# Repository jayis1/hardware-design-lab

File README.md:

# Hardware Design Lab

Author: jayis1

Full-cycle, open-source hardware device designs — from concept to KiCad schematics to production firmware to companion mobile apps. Every device is fully open: schematics, board layouts, C/Python firmware, and React Native apps. Each device lives in its own subfolder with complete deliverables.

## What's Inside Every Device

Every device folder contains the full stack — not just docs, but real buildable artifacts:

| Category | Files | Description |
|---|---|---|
| **Engineering Docs** | `phase1_conceptual_architecture.md` → `phase4_software_stack.md` | 4-phase design process: requirements, BOM & netlists, PCB layout rules, software stack |
| **KiCad Schematics** | `kicad/*.kicad_pro`, `*.kicad_sch`, `*.kicad_pcb` | Full schematic with real component symbols, net labels, power flags, and board outline with placed footprints |
| **C/Python Firmware** | `firmware/main.c`, `registers.h`, `board.h`, `drivers/`, `Makefile` | Production-quality MCU firmware — init code, drivers with DMA, USB descriptors, wire protocol |
| **React Native App** | `app/App.js`, `screens/`, `components/`, `utils/protocol.js`, `package.json` | Companion mobile app for device control, configuration, and status display |

## Design Methodology

Every device follows the same rigorous 4-phase process:

| Phase | Document | Contents |
|---|---|---|
| **Phase 1** | `phase1_conceptual_architecture.md` | Purpose, performance targets, constraints, block diagram, bus topology, power domains |
| **Phase 2** | `phase2_component_selection_schematics.md` | BOM with real part numbers, pinouts/MUX tables, decoupling networks, netlists, impedance matching |
| **Phase 3** | `phase3_pcb_blueprints_layout.md` | PCB stackup, routing rules, length matching, via strategy, thermal management, DFM notes |
| **Phase 4** | `phase4_software_stack.md` | MMIO/register defs, clock & GPIO init (production C), critical device driver, device tree, bootloader |

## Devices

| # | Device | Status | Description |
|---|---|---|---|
| 1 | [`eag-7000/`](eag-7000/) — Edge AI Gateway | ✅ Docs complete, KiCad/firmware/app pending | i.MX8MP + Hailo-8 NPU, 30 TOPS, fanless industrial, 2×2.5GbE, CAN-FD |
| 2 | [`chronos-rtk/`](chronos-rtk/) — Dual-Frequency RTK GNSS Receiver | ✅ Complete | ZED-F9P + STM32L4 + LoRa mesh, cm-level positioning, 868/915 MHz ISM |
| 3 | [`vortex-sdr/`](vortex-sdr/) — Portable SDR Spectrum Analyzer | ✅ Complete | STM32H743 + iCE40UP5K FPGA + ADF4351 PLL, 100kHz–6GHz, dual-FFT waterfall |
| 4 | [`web-slack-ledger/`](web-slack-ledger/) — WebSlack Ledger | Build-tested prototype; physical validation pending | Two-encoder differential travel and reversal ledger for slow hand-fed strip fixtures |
| 5 | [`slip-window/`](slip-window/) — Slip Window | Build-tested prototype; physical validation pending | Slip-casting cradle residence, interrupted draining, longest drain segment, and mold-opening notebook |
| 6 | [`stencil-orbit/`](stencil-orbit/) — Stencil Orbit | Build-tested prototype; physical validation pending | Manual screen-printing carousel station index, registration continuity and per-station tool-use notebook |
| 7 | [`crossover-track/`](crossover-track/) — Crossover Track | Build-tested prototype; physical validation pending | Four-contact cart trial recorder and guided ABBA lane-swap comparison separating cart and lane time contrasts |
| 8 | [`takeup-atlas/`](takeup-atlas/) — Takeup Atlas | Build-tested prototype; physical validation pending | Two-shaft reversal trials recording first output response, three-edge confirmation and rejected attempts in hand-operated mechanisms |
| 9 | [`chord-window/`](chord-window/) — Chord Window | Build-tested prototype; physical validation pending | Four-switch chord press spread, shared hold and release timing before keyboard filtering, with local policy comparison |
| 10 | [`detent-loop/`](detent-loop/) — Detent Loop | Build-tested prototype; physical calibration pending | Hand-operated sliding-catch force–travel loops with explicit zero, turnaround, signed work and local evidence export |
| 11 | [`tilt-break/`](tilt-break/) — Tilt Break | Build-tested prototype; physical calibration pending | Manual incline home-departure resistance brackets and independently qualified downstream puck arrival |
| 12 | [`pipette-path/`](pipette-path/) — Pipette Path | Build-tested prototype; physical training validation pending | Two-stop manual pipette plunger sequence recorder with operator-declared source immersion; not a volume calibrator |
| 13 | [`flow-pause/`](flow-pause/) — Flow Pause | Build-tested prototype; physical validation pending | Declared-supply hopper discharge silence, intervention precedence and recovery notebook; not a blockage detector |
| 14 | [`sieve-shuttle/`](sieve-shuttle/) — Sieve Shuttle | Build-tested prototype; physical validation pending | Four-zone manual sieving motion matrix, opposite-axis traversals, same-zone returns and longest directional runs; not separation efficiency |
| 15 | [`bellows-phase/`](bellows-phase/) — Bellows Phase | Build-tested prototype; physical validation pending | Direction-conditioned inlet/outlet flap-position intervals across manual bellows strokes; not airflow or efficiency |
| 16 | [`shutter-quartet/`](shutter-quartet/) — Shutter Quartet | Build-tested prototype; optical validation pending | Four-point fragmented exposure, missing-point and reopening notebook for slow hand-operated teaching shutters; not camera calibration |
| 17 | [`coupon-transit/`](coupon-transit/) — Coupon Transit | Build-tested prototype; physical validation pending | Two-holder rack-to-rack transfer durations, same-rack returns and interrupted-observation notebook; not specimen identity or treatment verification |
| 18 | [`pattern-sled/`](pattern-sled/) — Pattern Sled | Build-tested prototype; physical validation pending | Three-track mechanical program-strip repeat comparator with a learned sixteen-word reference, per-position mismatches and terminal alignment-loss diagnostics |
| 19 | [`kit-multiset/`](kit-multiset/) — Kit Multiset | Build-tested prototype; physical validation pending | Tray-delimited unordered 2:1:1 bin-paddle recipe declarations, conservative abandonment and local evidence export; not inspected part quantities |
| 20 | [`shim-bracket/`](shim-bracket/) — Shim Bracket | Build-tested prototype; physical validation pending | Indexed feeler-gauge fit/refusal declarations with persistent monotonicity contradictions; not calibrated gap measurement |
| 21 | [`catch-witness/`](catch-witness/) — Catch Witness | Build-tested prototype; physical validation pending | Settled-latch reopening notebook with expiring handle/tug associations and separate unseated, unexplained and aborted outcomes; not a retention-force gauge |
| 22 | [`beat-aperture/`](beat-aperture/) — Beat Aperture | Build-tested prototype; physical validation pending | Two-pendulum return apertures retaining zero, single and multiple comparison returns within each reference cycle; not continuous phase measurement |
| 23 | [`grip-lattice/`](grip-lattice/) — Grip Lattice | Build-tested prototype; physical validation pending | Footswitch-delimited three-zone dummy-handle contact combinations, segment lengths and explicit unknown intervals; not a force or ergonomic assessment instrument |

---

New design: [Code Margin](code-margin/) — a four-contact code-separation workbench with minimum-distance witnesses and explicit single-contact-error ambiguity. Target build, software tests and electrical CAD checks passed; physical validation is pending. Author: jayis1.

Previous design: [Step Islands](step-islands/) — a four-contact configuration exploration fixture with single-change islands, bridge candidates and shortest candidate paths. Target build, software tests and electrical CAD checks passed; physical validation is pending. Author: jayis1.

## EAG-7000 — Edge AI Gateway

A high-performance, fanless industrial Edge AI Gateway for real-time ML inference at the network edge.

### System Specifications

| Parameter | Value |
|---|---|
| **AI Throughput** | ≥30 TOPS INT8 (2.3 TOPS SoC + 26 TOPS Hailo-8) |
| **CPU** | NXP i.MX8M Plus — 2× Cortex-A72 @ 2.0 GHz + 1× Cortex-M4F @ 800 MHz |
| **Memory** | 2× Micron MT53D512M32D4DS — 8GB LPDDR4X @ 4267 MT/s |
| **Storage** | 32GB eMMC 5.1 (boot) + 128GB NVMe M.2 2242 (data) |
| **Networking** | 2× 2.5GbE (AQR111C) + 1× 5GbE USB-C |
| **Industrial IO** | 2× CAN-FD, 3× SPI, 4× I2C, 5× UART, 1× MIPI-CSI2 |
| **Power** | 12V DC / PoE+ (802.3at), ≤15W typical, 25W peak |
| **Form Factor** | 100mm × 72mm × 25mm, DIN-rail mountable |
| **Operating Temp** | -40°C to +85°C (industrial) |

### Key Design Decisions

1. **i.MX8M Plus** over Rockchip RK3588 — 15-year industrial availability, verified -40°C to 85°C
2. **LPDDR4X** over DDR4 — 1.1V IO for passive cooling at 15W TDP
3. **eMMC boot** over SD card — vibration reliability in industrial environments
4. **Hailo-8 M.2** accelerator — 26 TOPS at 2.5W, best TOPS/W in form factor
5. **Dual CAN-FD via SPI** (MCP2518FD) — M4F handles real-time fieldbus with <1ms response

## Vortex-SDR — Portable SDR Spectrum Analyzer

A portable, handheld spectrum analyzer covering 100 kHz to 6 GHz with dual-channel FFT, real-time waterfall display, capacitive touchscreen, and BLE companion app. Designed for RF engineers, ham radio operators, and EMC compliance testing.

### System Specifications

| Parameter | Value |
|---|---|
| **Frequency Range** | 100 kHz – 6 GHz (dual-conversion superheterodyne) |
| **MCU** | STM32H743ZIT6 — Cortex-M7 @ 480 MHz, 1MB Flash, 1MB RAM |
| **FPGA** | Lattice iCE40UP5K — FFT/waterfall acceleration |
| **PLL Synthesizer** | ADF4351 — 35 MHz to 4.4 GHz (6 GHz with ADF5002 prescaler) |
| **ADC** | AD9645 — 14-bit, 61.44 MSPS dual-channel |
| **Display** | ILI9341 — 2.8" 320×240 TFT with capacitive touch |
| **BLE** | nRF52840 — 2 Mbps BLE 5.0 companion link |
| **Power** | 3.7V LiPo (TPS62A02 buck + AMS1117 LDO), USB-C charging |
| **Form Factor** | 120mm × 75mm × 18mm, handheld |
| **Operating Temp** | -20°C to +55°C (commercial) |

### Key Design Decisions

1. **STM32H743** over STM32F4 — Cortex-M7 @ 480 MHz for real-time FFT processing, dual-issue FPU
2. **iCE40UP5K FPGA** for FFT offload — 5280 LUTs, on-chip RAM for windowing and averaging
3. **Dual-conversion architecture** — 1st LO (ADF4351) + 10.7 MHz IF for image rejection
4. **AD9645 dual ADC** — simultaneous I/Q sampling, 14-bit resolution for dynamic range
5. **Battery-powered with USB-C** — TPS62A02 2A buck for efficiency, MCP73871 charger

## License

| Component | License |
|---|---|
| Hardware design (KiCad) | CERN-OHL-S v2 |
| C firmware & drivers | GPL-2.0 |
| Python tools & scripts | MIT |
| React Native companion apps | MIT |

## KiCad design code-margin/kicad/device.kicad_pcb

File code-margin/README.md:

# Code Margin — empirical contact-code separation workbench

Author and creator: jayis1

Copyright (c) 2026 jayis1. Original software, documentation and locally authored electrical sources are MIT licensed; see LICENSE. Installed KiCad footprint geometry retains its upstream licensing. Revision A is an unbuilt engineering prototype. Target compilation, synthetic acquisition, desktop operation and electrical CAD checks are reproducible. No board has been fabricated, physical target programmed, contact fixture calibrated or real workshop trial performed. This is not a safety interlock, certified identifier or manufacturing release.

## Purpose and practical value

Code Margin helps a maker examine the error margin of a small mechanical coding scheme before embedding that scheme in a product. Four independent voltage-free contacts read four raised tabs, magnetically operated reeds or position witnesses. The instrument keeps every sufficiently stable four-bit word it encounters. It computes the minimum Hamming distance between distinct retained words, shows an actual closest pair, and lists all hypothetical readings that could have come from more than one retained word after at most one changed contact. The companion's reading inspector makes the ambiguity tangible without silently correcting a measurement.

Imagine interchangeable educational tiles whose underside tabs operate four switches. Two tiles might look sufficiently different on paper while producing electrical words that differ at only one switch. A dirty contact on one tile can then produce the exact retained code of another. A simple binary display shows both words but does not explain the consequence. Code Margin preserves that pair and shows which channels distinguish it. If the designer changes the tab arrangement, a separate session can reveal whether the new observed words are better separated. The tool does not establish which physical tile owns a word; an experimenter must keep that correspondence separately.

A second use is a low-energy mechanical selector demonstrator. A builder may intend only two resting states, all-open and all-closed, yet a repeatable intermediate pause adds another stable word. Rather than excluding that inconvenient observation, this instrument retains it and recomputes the reduced separation. The result invites inspection of the linkage, witness placement or experimental protocol. A stable transient is not automatically an intended code, and the notebook does not pretend to know the designer's intent. Its conservative retained set is evidence about observed electrical words, not an approved list of identities.

Target users include makers of removable teaching inserts, museum demonstrator builders, mechanical-computing educators and workshop engineers prototyping disconnected position coding. They can compare contact placement, tab patterns or assembly conditions without a cloud account. A useful session begins with documented contact meanings, a manually checked fixture and a list of intended physical objects. Practical benefit remains a hypothesis to evaluate with users. The proposed contribution is making small code-space vulnerabilities visible while collecting the physical observations that motivated them.

## Originality, alternatives and boundaries

Before selecting this concept, the configured main branch was pulled, device directories were listed and README titles were inventoried. The closest designs were inspected. Insert Code uses a fixed constant-weight code and retains the first identity through a docking episode. Mask Key evaluates which of three controls can explain a separately observed binary response. Step Islands constructs connectivity through single-bit graph edges. Code Margin instead treats all four channels equally and asks how closely distinct observed words lie and where their radius-one error neighborhoods overlap. It has no response channel, docking identity latch or transition-path claim.

Coding theory and coded position sensors are established prior art. A bounded search found “Error-detecting unit-distance code,” DOI https://doi.org/10.1109/19.58616, and “On Hamming distance of partial M-sequence with application to absolute encoder,” DOI https://doi.org/10.1109/iecon.1991.239090. These results directly limit novelty claims: neither Hamming distance nor error-aware mechanical encoding is new. This repository contribution is the particular physical exploration workflow, retained-evidence contract and local ambiguity interface. Worldwide uniqueness, patentability and freedom to operate have not been established.

A paper worksheet is sufficient for a few predetermined codes. A general-purpose logic analyzer and script can perform similar analysis at much higher speeds. RFID and barcodes offer many more identities and metadata. Video records physical context that four contacts cannot. Code Margin is appropriate only when transparent, slow, four-channel observations make an early mechanical experiment easier. Its reused carrier is not claimed as a new circuit topology. No application should replace independent safety sensing or authenticated identification with this instrument.

## Hardware specifications

The controller is a separately purchased ST NUCLEO-F401RE, MB1136 family, with an STM32F401RET6 Cortex-M4, 512 KiB flash and 96 KiB SRAM. Firmware establishes the nominal 16 MHz internal HSI clock and observes one-millisecond SysTick increments. USART2 sends telemetry at 115200 baud, eight data bits, no parity and one stop bit. The ST-LINK USB virtual COM bridge supplies the computer connection. There is no radio, battery, charging circuit, cloud service, actuator, command receiver or nonvolatile experiment storage.

The custom PCB is a cable-connected passive interface, not a standalone microcontroller board or mechanically mating Arduino shield. Its closed outline is 80 by 70 mm, with two copper layers and nominal 1.6 mm FR-4 thickness. Six through-hole headers and eight axial resistors provide four independently pulled-up contact channels. The Nucleo supplies voltage regulation, processor decoupling, reset, debugging and USB bridging. Those required functions belong to the purchased board rather than being omitted from a purported complete MCU circuit.

Each sense node has a 10 kilohm pull-up to regulated 3.3 V and a 1 kilohm series path to its external contact. The other contact terminal connects to shared ground. Closed contacts therefore read electrical low and logical one. A low-level lever switch such as Omron D2F-01L is a candidate, subject to mounting and low-current verification. Reed contacts are another possibility but require magnetic threshold and hysteresis characterization. This package does not claim a qualified switch lot, a completed mechanical fixture or a production-ready enclosure.

## Architecture and wiring

    Four tab / position witnesses A, B, C, D
                         |
                    J3 through J6
                         |
              1k series / 10k pull-up
                         |
                     J2 GPIO harness
                         |
             External NUCLEO-F401RE
                         |
          100 ms whole-word qualification
                         |
            Retained sixteen-word bitset
                         |
          Minimum distance + closest pair
            Radius-one ambiguity analysis
                         |
              CM1 + CRC / USART2 TX
                         |
                 ST-LINK USB VCP
                         |
       Linux Tk app: code table / reading inspector
              acquisition / replay / CSV

J1 pin one connects to Nucleo CN6 pin four, regulated 3V3; J1 pin two connects to CN6 pin six, ground. J2 pins one through four connect respectively to CN8 pins one through four: PA0/A0, PA1/A1, PA4/A2 and PB0/A3. The analog-labelled connector positions are configured as digital inputs. J3, J4, J5 and J6 are POSITION_A, POSITION_B, POSITION_C and POSITION_D. Every contact connector uses pin one for signal and pin two for ground. Check this harness independently; connector pitch does not prevent reversal.

The numeric word is A + 2*B + 4*C + 8*D. The app prints A B C D in that named order rather than conventional most-significant-bit-first notation. Thus word three is printed as 1 1 0 0. A retained-set bit at position w means word w was observed. There are sixteen possible words, not sixteen independently instrumented objects. Two physical objects that produce the same word collapse into one set member and are not distinguishable by this system.

PA2 uses alternate function AF7 for USART2 transmit. Inspect the purchased board revision and ST-LINK virtual-COM solder bridges, including SB13/SB14 and SB62/SB63, before use. ST UM1724 provides the connector tables; RM0368 describes the STM32F401 register map, and PM0214 describes Cortex-M4 support. A copy of UM1724 was downloaded during verification from https://embedded.fel.cvut.cz/sites/default/files/procesory/STM32/um1724-stm32-nucleo64-boards-mb1136-stmicroelectronics.pdf. The manufacturer's document is https://www.st.com/resource/en/user_manual/um1724-stm32-nucleo64-boards-mb1136-stmicroelectronics.pdf. Neither document substitutes for inspecting the actual assembly.

## BOM, power and physical limits

R1, R3, R5 and R7 are 10 kilohm one-percent axial pull-ups. R2, R4, R6 and R8 are 1 kilohm one-percent axial series resistors. The DIN0207 resistor footprints have 7.62 mm lead spacing. J1 and J3 through J6 use two-position 2.54 mm vertical headers; J2 uses a four-position header. The connectivity manifest records all on-carrier references, values, footprints and pin nets. Add the development board, its USB cable, four suitable contacts, insulated wiring, cable strain relief and a nonconductive enclosure.

At nominal values, a closed channel draws 3.3 V divided by 11 kilohms, or 0.30 mA, and its sense voltage is approximately 0.30 V. Four closed channels draw 1.20 mA from the regulated rail. These are calculations, not measurements. Development-board and debugger consumption dominate the total USB budget and must be measured with the actual unit. The low excitation current may be insufficient to penetrate oxide on contacts designed for larger wetting currents. An apparent open bit can be a contact-quality problem rather than a different mechanical code.

Mount witnesses on adjustable insulating supports and keep tabs or magnets captive. Contact force must not substantially change the mechanism under study. Keep wiring short, label both ends and photograph the physical code arrangement for each session. The PCB has no mounting holes; use insulating edge supports rather than drilling through reviewed copper. Provide safe access to reset and USB. Mechanical tolerances, switch overtravel, magnet spacing and enclosure fit remain application-specific commissioning work, not verified dimensions in this release.

Only detached voltage-free switches may connect to the carrier. It has no galvanic isolation, reverse-polarity protection, surge suppressors or adequate external-voltage protection. USB ground is common to all contacts. Never attach powered logic, industrial wiring, vehicle circuits, mains or live machine interlocks. Wire with power removed, check rail resistance and connector orientation, and apply only the Nucleo's regulated 3.3 V. Open wiring resembles an open switch; shorted wiring resembles closure. Perform a manual channel check before every experiment.

## Firmware implementation and acquisition contract

Firmware is freestanding C11, built with GNU Arm Embedded tools and warnings treated as errors. startup.c provides vectors, reset initialization and memory support; linker.ld maps flash and SRAM. registers.h defines the used MMIO locations. board.h states the external connection contract. The drivers configure GPIO, clock, watchdog and a bounded nonblocking transmitter. main.c acquires newly observed ticks and schedules status transmission. There is no heap, RTOS or vendor SDK dependency.

The platform is explicitly reused from jayis1's Step Islands at commit 181a193a02a4996b943970ee9c643f40ece0d9ca. Acquisition, startup, serial framing, passive hardware generation and the desktop transport shell are shared infrastructure. Code Margin adds its own distance, witness and ambiguity analysis, protocol interpretation, reading inspector and exhaustive tests. tools/import_platform.py records provenance and refuses overwrites; it is not a normal build command and does not recreate subsequent edits. The electrical generator remains separately reproducible.

The first acquired sample establishes an endpoint without credit. A word qualifies after one hundred consecutive unchanged one-millisecond intervals: an initial endpoint plus one hundred subsequent samples. Qualification adds one visit and retains that word. Further holding adds qualified interval time, not repeated visits. A raw change restarts qualification, including a short glitch that never becomes a retained word. The qualification-completing interval remains unknown rather than being retroactively counted as settled dwell. Whole-word qualification prevents independently delayed bits from inventing a configuration never observed together.

Skipped ticks add gap and missed-sample diagnostics and restart qualification. Retained history survives, but absent intervals do not receive inferred exposure. Every acquired endpoint after initialization is classified as unknown, qualified or a gap endpoint. Updates are transactional so a counter overflow cannot publish half a visit. Terminal faults retain their first cause and freeze experimental evidence; timestamps and transmission diagnostics may continue. Fault codes are zero normal, one pin configuration, two watchdog initialization, three invalid raw input and four exhaustion. Reset erases volatile history.

## Distance, ambiguity and interpretation

For retained distinct words a and b, Hamming distance is the number of unequal contacts, implemented as population count of a XOR b. The minimum is taken over every distinct pair. The closest-pair witness uses numeric tie-breaking. Empty and singleton histories have no pair; wire value five means undefined, not five-bit protection. The UI prints undefined. A newly retained word can reduce the minimum distance, but repeated visits cannot improve it. Removing an inconvenient observation requires a new explicitly separate session, not editing the evidence in place.

For each hypothetical received word r, the candidate set contains every retained word whose distance from r is at most one. Zero candidates means outside the restricted radius-one model. One means a unique candidate under that model, not verified object identity. Two or more means ambiguity, including when r exactly equals a retained word. Exact membership must not override the fact that a neighboring code could have produced the same reading through a single error. The ambiguous mask has bit r set precisely for those multiple-candidate readings.

For example, the two retained words zero and fifteen have minimum distance four and disjoint radius-one neighborhoods. Reading one has only zero as a radius-one candidate; reading three has no candidate. Adding word one reduces the minimum to one, and readings zero and one become ambiguous. The firmware constructs each radius-one neighborhood from the reading and its four single-bit flips. The companion independently recomputes candidates by scanning retained words. Both implementations are checked across every possible retained set, not just a few selected codebooks.

In an ideal complete codebook, minimum distance at least two detects any single-bit substitution through membership checking, and minimum distance at least three separates single-error neighborhoods. These mathematical statements do not establish that the observed set is complete, that only one contact can fail, or that a physical object has the intended code. Correlated wiring faults, hidden objects and unobserved states break those assumptions. The instrument therefore never performs automatic correction, commands machinery or issues a safe-to-use verdict.

A generic unobserved-word hint remains available to help inspect coverage. It chooses the unobserved word nearest the current raw word, with numeric ties; sixteen means none remain. It is not a request to manufacture every code or optimize a codebook. Record a hinted word only if it represents a relevant freely achievable condition. Idle or intermediate words held long enough also enter the history. Keep that conservative evidence, annotate its physical meaning externally, and use separate sessions for changed fixtures. The desktop inspector is the nonmutating way to explore hypothetical errors.

## Protocol and companion application

CM1 telemetry contains eighteen unsigned decimal fields in this order: now, samples, gaps, missed, tx_errors, raw, hold, credited, seeded, fault, visits, settings, coverage, qualified_ms, unknown_ms, suggestion, distance and ambiguous. The body begins with CM1 and comma-separated values. An asterisk, four uppercase hexadecimal CRC digits and newline terminate the record. CRC-16/CCITT-FALSE uses initial value 65535 and polynomial 0x1021 over the body before the asterisk. CRC detects corruption but does not authenticate the sender.

settings is the retained sixteen-bit code set. coverage repeats that set for the common acquisition contract. distance is a value from one through four or the undefined sentinel five. ambiguous is a sixteen-bit reading mask, not a count of physical errors. The companion recomputes summaries, checks ranges and conservation, and enforces necessary acquisition transition bounds. Dense adjacent observations receive exact qualification and credit-attribution checks. Sparse validation cannot reconstruct every hidden sample or prove that a recording came from real hardware.

Run `python3 code-margin/app/main.py` on Linux with Tk installed. The Code margins tab shows every possible reading, whether it was observed, its radius-one status and all candidate codes. The Reading inspector accepts a hypothetical integer zero through fifteen and shows the candidate list without changing evidence. Acquisition / limits presents counters and caveats. Connect opens the selected serial port; Disconnect retains the session. A second connection is refused while a port is owned. Failed opens preserve prior evidence and restore terminal attributes where applicable.

Replay accepts only regular files up to two MiB and rejects empty recordings, malformed decimals, bad checksums, impossible summaries and partial tails. Live parsing can resynchronize on the complete CM1 marker after corruption. Freshness tracks acquisition progress separately from byte reception. A two-second progress pause or excessive cumulative host/device clock disagreement closes the link and requires reconnect. There is no persistent boot identifier, so some resets remain indistinguishable from forward traffic. Uncalibrated oscillator drift can conservatively end a long live session.

Export CSV exclusively creates a new file with private permissions, refusing overwrite. It includes author jayis1, provenance, connection state, warnings, parser diagnostics, progress age, total accepted rows and the latest two thousand snapshots. The retained set permits later reconstruction of every candidate neighborhood. Inspector queries are views, not acquired events. Save evidence before reset and keep physical object labels, contact placement and experimental conditions beside it. Synthetic fixtures remain synthetic even when accepted by the actual GUI.

## Build, verification and commissioning

From the repository root run `make -C code-margin/firmware clean all test fixture`. This builds an ARM ELF and binary, runs sanitized C tests and generates a synthetic CM1 recording. Run `xvfb-run -a python3 -m unittest discover -s code-margin/tests -p 'test_app.py' -v` for model, serial and desktop tests. The test suite covers every retained codebook and reading, minimum-distance witnesses, qualification boundaries, gaps, wrap, terminal faults, real C-encoded replay, malformed frames, live PTYs, reconnect, stale acquisition and private exports. No external Python package installation is required; the GUI needs system Tk and the headless tests need Xvfb.

Generate CAD using `/usr/bin/python3 code-margin/tools/generate_hardware.py` with KiCad 9 bindings and footprint libraries. Validate using `/usr/bin/python3 code-margin/tools/check_hardware.py`. The checker runs native ERC and DRC, exports a fresh schematic XML netlist, and compares every reference, value, footprint and pin net with PCB pads and the manifest. Passive-only ERC cannot validate the external Nucleo or harness. Build outputs and local KiCad preferences are ignored. Exact execution results are recorded in VALIDATION.md.

Before fabrication, review the electrical and mechanical design independently. After assembly, inspect soldering, check rail resistance, verify the harness and measure open and closed input voltages. Program through ST-LINK only after confirming target and power selection; the optional Makefile flash target uses OpenOCD. Exercise all sixteen raw words, introduce chatter and missed acquisitions, and measure the worst-case foreground latency during telemetry. Nominal one-millisecond scheduling is not a measured timing guarantee.

Finally, compare a small known set of physical inserts with synchronized manual notes. Verify that the retained words correspond to the intended contact configurations, that switch loading does not alter seating, and that different physical objects sharing a code remain visibly documented as indistinguishable. Deliberately open one contact to explore ambiguity without introducing powered faults. The supplied source package supports that evaluation; it does not claim that a fabricated unit or practical user trial has already passed it.

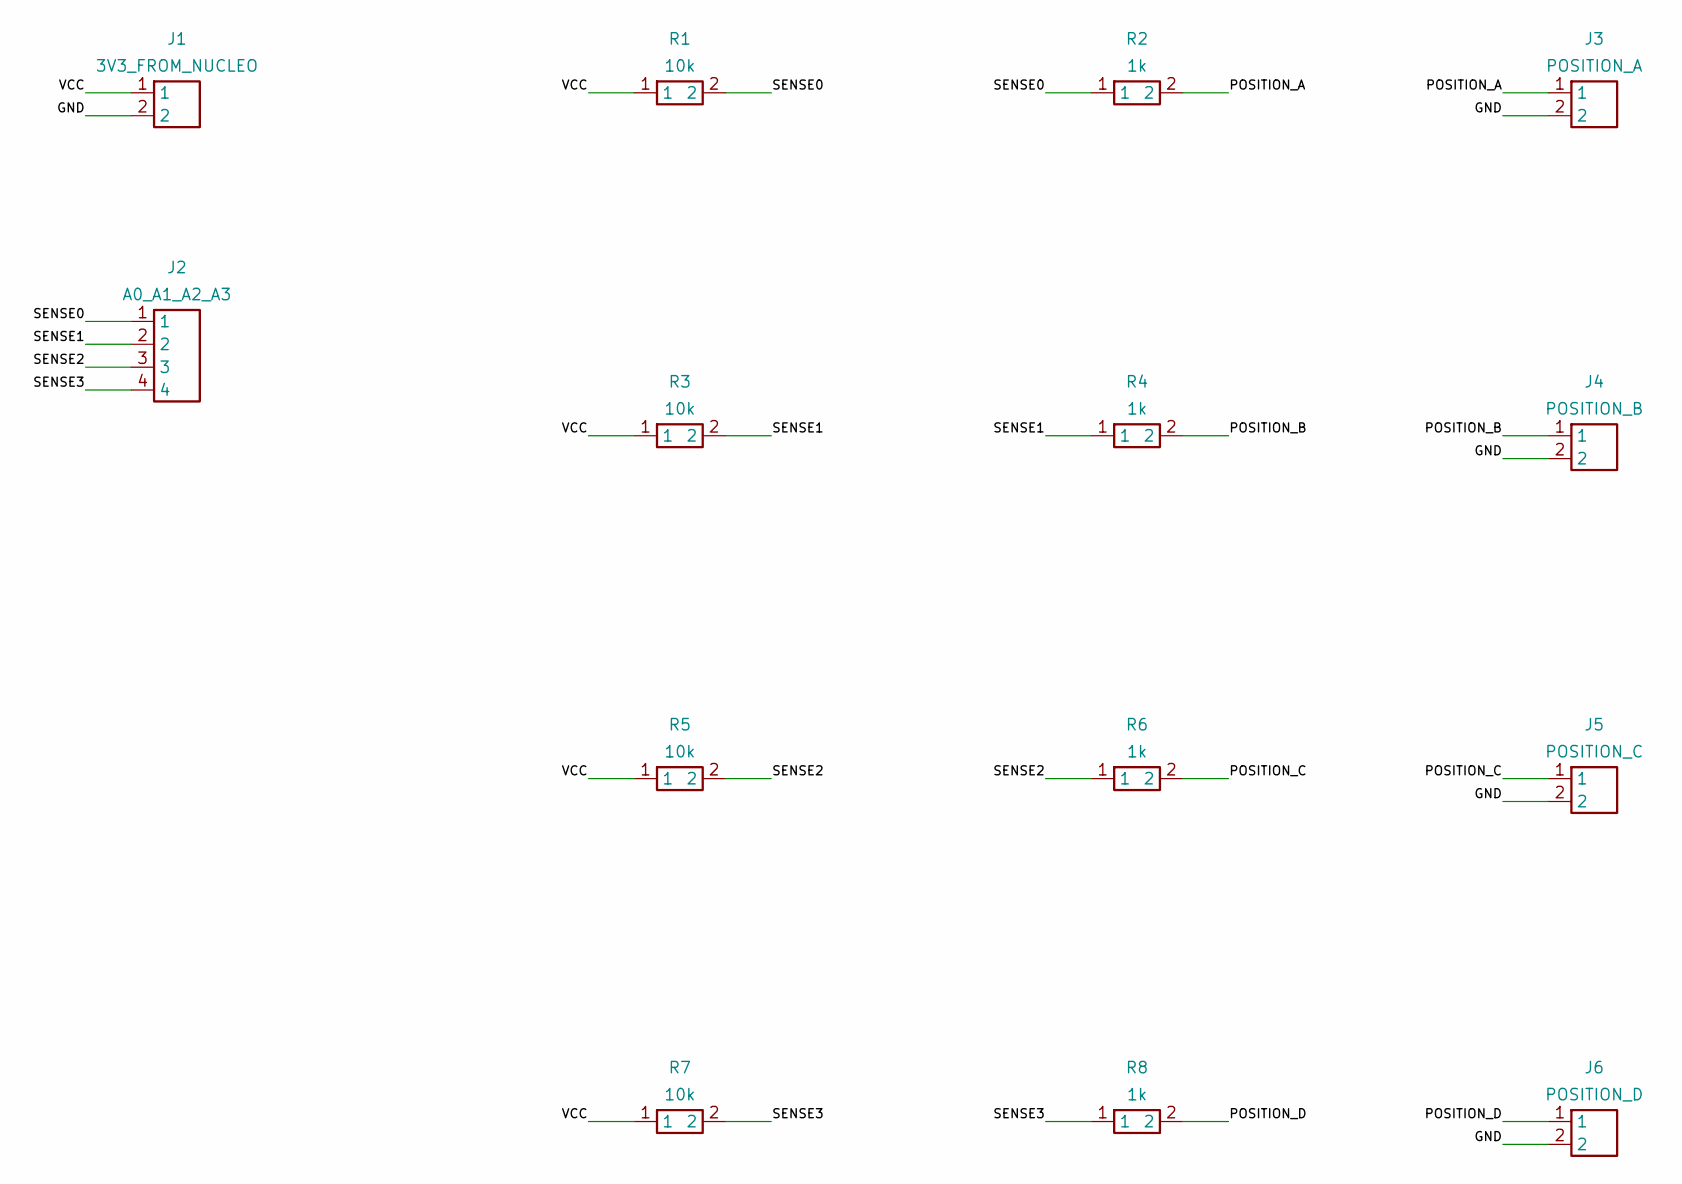
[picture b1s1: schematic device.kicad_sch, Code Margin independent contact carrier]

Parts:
J1: 3V3_FROM_NUCLEO; PinHeader_1x02_P2.54mm_Vertical
J2: A0_A1_A2_A3; PinHeader_1x04_P2.54mm_Vertical
J3: POSITION_A; PinHeader_1x02_P2.54mm_Vertical
J4: POSITION_B; PinHeader_1x02_P2.54mm_Vertical
J5: POSITION_C; PinHeader_1x02_P2.54mm_Vertical
J6: POSITION_D; PinHeader_1x02_P2.54mm_Vertical
R1, R3, R5, R7: 10k; R_Axial_DIN0207_L6.3mm_D2.5mm_P7.62mm_Horizontal
R2, R4, R6, R8: 1k; R_Axial_DIN0207_L6.3mm_D2.5mm_P7.62mm_Horizontal

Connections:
GND: J1.2, J3.2, J4.2, J5.2, J6.2
POSITION_A: J3.1, R2.2
POSITION_B: J4.1, R4.2
POSITION_C: J5.1, R6.2
POSITION_D: J6.1, R8.2
SENSE0: J2.1, R1.2, R2.1
SENSE1: J2.2, R3.2, R4.1
SENSE2: J2.3, R5.2, R6.1
SENSE3: J2.4, R7.2, R8.1
VCC: J1.1, R1.1, R3.1, R5.1, R7.1

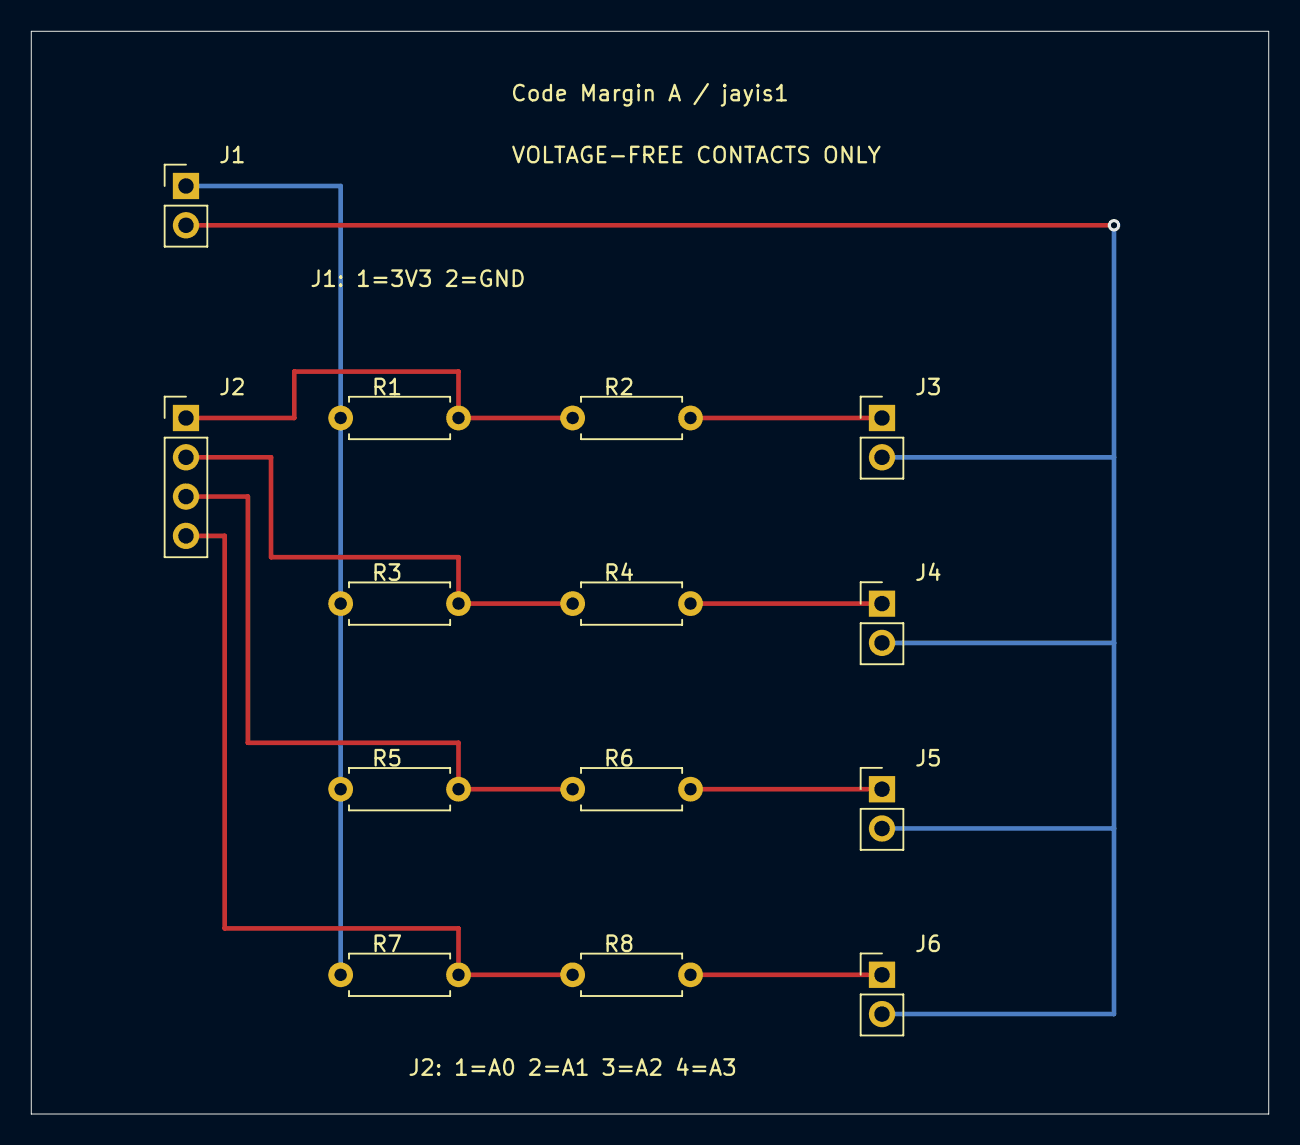
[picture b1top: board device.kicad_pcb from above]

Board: 2 copper layers, 80.0 x 70.0 mm, 14 parts (0 on the bottom side), 10 nets.

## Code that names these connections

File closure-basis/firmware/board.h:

/* Author: jayis1. SPDX-License-Identifier: MIT */
#ifndef CLOSURE_BOARD_H
#define CLOSURE_BOARD_H
#include <stdint.h>
#include <stddef.h>
#include <stdbool.h>
#define CORE_HZ 16000000u
#define SERIAL_BAUD 115200u
#define SERIAL_BUFFER 1024u
/* External NUCLEO-F401RE MB1136. J1: CN6.4 3V3 / CN6.6 GND.
 * J2: CN8.1..4 PA0/PA1/PA4/PB0. J3..6: POSITION_A, POSITION_B, POSITION_C, POSITION_D.
 * Every contact connector: pin1 signal, pin2 GND; voltage-free dry contacts only.
 * USART2 TX PA2 AF7 to ST-LINK VCP. No command receiver. */
bool board_clock_reset(void);
bool board_inputs_configured(void);
void board_init(void);
uint32_t board_millis(void);
uint8_t board_closed(void);
bool board_watchdog_start(void);
void board_watchdog_feed(void);
bool serial_submit(const char *data, size_t size);
void serial_poll(void);
bool serial_busy(void);
bool serial_take_timeout(void);
#endif

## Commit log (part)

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2026-06-12 EAG-7000 Edge AI Gateway - Complete 4-phase design
    Phase 1: Conceptual architecture, block diagram, bus topology, power domains
    Phase 2: BOM, SoC pinouts, netlists, decoupling networks, impedance matching
    Phase 3: 10-layer PCB stackup, DDR/PCIe/USB routing rules, thermal management
    Phase 4: Bootloader strategy, MMIO/register defs, clock/GPIO init, MCP2518FD CAN-FD driver
2026-06-12 Restructure: rename repo to hardware-design-lab, move EAG-7000 into subfolder, update root README as index of all devices
2026-06-12 Update README — open everything: KiCad schematics, C/Python firmware, React Native apps
2026-06-13 Enhance eag-7000 — add KiCad schematics, firmware, and companion app
2026-06-14 Add Chronos-RTK: dual-frequency RTK GNSS receiver with LoRa mesh
    Complete hardware/software design for a high-precision RTK GNSS receiver board:
    - ZED-F9P dual-frequency (L1/L2) GNSS receiver for cm-level positioning
    - STM32G474RET6 Cortex-M4F MCU as system controller
    - SX1262 LoRa transceiver for RTCM correction relay (868/915 MHz)
    - W25Q128 16MB SPI NOR flash for observation logging
    - SSD1306 OLED 128x64 display for live status
2026-06-14 feat: add vortex-sdr — Portable SDR Spectrum Analyzer (100kHz–6GHz)
2026-06-14 Add NeuroLink: 32-channel biosignal acquisition system
    Complete hardware design for a 32-channel EMG/EEG/ECG biosignal
    acquisition platform featuring:
    - 8× ADS1299 24-bit ΔΣ ADCs (daisy-chained, simultaneous sampling)
    - STM32H743ZIT6 Cortex-M7 @ 480 MHz main MCU
    - iCE40UP5K FPGA for real-time DSP pipeline
    - nRF52840 BLE 5.0 wireless streaming
2026-06-14 Add RideCore: 48V/200A PMSM motor controller for light EVs
    Complete hardware design with:
    - Phase 1-4 architecture documents (concept, components, PCB, software)
    - KiCad project/schematic/PCB with 6-layer stackup
    - STM32G474 firmware: FOC, PMIC driver, CAN FD driver (DMA), SPI flash, BLE UART
    - React Native companion app: dashboard, tuning, diagnostics, settings
    - Binary wire protocol with CRC16-CCITT
2026-06-14 feat: SkyPilot dual-IMU drone flight controller with 4G/LTE telemetry
    Complete hardware design for a professional-grade drone flight controller:
    - STM32H743VIT6 (480MHz Cortex-M7) flight core
    - Dual redundant IMU: ICM-42688-P (primary) + BMI270 (secondary)
    - u-blox LARA-R6401 Cat.4 LTE modem for BVLOS telemetry
    - SAM-M10Q multi-constellation GNSS
    - BMP390 barometric altimeter
2026-06-14 feat: add HexaScope — 6-channel mixed-signal oscilloscope
    Complete hardware design for HexaScope, a portable 6-channel mixed-signal
    oscilloscope / logic analyzer with:
    - 4 analog channels (250 MS/s, 100 MHz BW, ADS61B49 ADCs)
    - 2 digital channels (200 MS/s, LT1715 comparators)
    - Lattice ECP5-5G FPGA for real-time triggering and protocol decode
    - STM32G474 MCU for control plane (SPI, I²C, USB)
2026-06-15 feat: add WaveForge polyphonic digital audio synthesizer engine
    Complete design for a 64-voice wavetable/FM/noise synthesizer board:
    Hardware:
    - STM32H743VIT6 (480 MHz Cortex-M7, 2 MB Flash, 1 MB RAM)
    - WM8778 24-bit audio codec (110 dB SNR, 48/96 kHz)
    - W25Q256 32 MB QSPI wavetable flash (XIP-capable)
    - TPA6130A2 headphone amplifier (128 dB SNR)
2026-06-15 feat: add CyberGuard — multi-protocol hardware security token
    Complete design for a FIDO2/WebAuthn authenticator with biometric fingerprint,
    NFC contactless, BLE 5.3, and USB-C connectivity in a keychain dongle form factor.
    - Phase 1: Conceptual architecture with STM32L562 (Cortex-M33), A71CH secure
    element, PN7150 NFC, FPC1025 fingerprint, nRF52833 BLE coprocessor, MX25R1635F
    QSPI flash, STPMIC1 PMIC — full bus topology and data flow diagrams
    - Phase 2: Complete BOM (20 components, ~1.20 @ 10K), pinout tables for all ICs,
2026-06-15 feat: add PicoRadar — 60GHz FMCW radar development platform
    IWR6843AOP radar SoC with on-package antennas, STM32H743VIT6 host
    processor, ESP32-C3 WiFi/BLE, LAN8720A Ethernet+PoE, ICM-42688-P IMU,
    SH1106 OLED display. Full design: 4-phase docs, KiCad schematics/PCB,
    C firmware with FreeRTOS + 2 DMA drivers, React Native companion app
    with binary wire protocol (CRC-16).
2026-06-15 Add Aether-Link: PCIe 4.0 x8 NVMe-oF/TCP Hardware Accelerator
    Complete hardware design for a PCIe add-in card with:
    - XC7K325T FPGA, dual 100GbE QSFP28, 8GB DDR4-3200 ECC
    - Full NVMe-oF/TCP offload engine with hardware TOE
    - 12-layer PCB design with impedance-controlled routing
    - MicroBlaze firmware with TOE, NVMe-oF PDU, and peripheral drivers
    - React Native companion app with telemetry dashboard
2026-06-15 Update designer credit in README
2026-06-16 Add Chronos Pulser — Precision TDR & Sub-Nanosecond Pulse Generator
    Complete hardware design for a portable USB-powered Time-Domain Reflectometer:
    - Lattice ECP5-45F FPGA with VexRiscv soft CPU
    - AD9230-250 12-bit 250MSPS ADC
    - 10ps TDC via carry-chain tapped delay line
    - MA44769 SRD + BFR92A avalanche pulse generator (65ps rise time)
    - FT601Q USB 3.0 bridge
2026-06-16 feat: add PhotonWeave — Real-Time CGH Accelerator Engine
    PhotonWeave is a PCIe FHHL card that computes holograms from 3D
    depth-map data in real time using an FPGA-based Angular Spectrum
    Method pipeline and drives a 4K spatial light modulator at 60 fps.
    Key specs:
    - XC7K325T-2FFG900C Kintex-7 FPGA (326K logic cells, 840 DSP)
    - 4x MT40A512M16JY-075E DDR4-2400 (16Gb, 76.8 GB/s)
2026-06-16 feat: add Nebula Matrix — Professional FPGA-Driven LED Matrix Display Engine
    Complete hardware/software design for a 256×256 RGB LED matrix controller:
    - XC7A100T FPGA + STM32H743 co-processor architecture
    - 16× HUB75E ports, 16-bit color, 120 Hz refresh, 1 GB DDR3L
    - Gigabit Ethernet (Art-Net/sACN), HDMI input, USB-C RNDIS, SD card
    - 6-layer PCB with controlled impedance, DDR3 length matching
    - Full C firmware (FreeRTOS, LWIP, TinyUSB, FatFS) with DMA drivers
2026-06-16 Fix author credit: change Nous Research to jayis1 across all devices
2026-06-16 Add terramesh: distributed subterranean geotechnical monitoring mesh for landslide and structural health early warning
2026-06-17 Add carbonflux: open-source soil CO2 flux & respiration monitor with STM32U5, SCD41 NDIR sensor, LoRaWAN, solar-ready power
2026-06-17 Add sonicsight: Portable Acoustic Tomography Scanner for Wood & Composite NDT
2026-06-17 Add FerroProbe: Open-source 3-axis vector fluxgate magnetometer for geophysical surveying with 0.1 nT resolution, GPS-tagged SD logging, IMU orientation compensation, and React Native companion app
2026-06-18 Add hydrofluor: submersible multi-wavelength UV-Vis fluorescence water quality sonde
    Author: jayis1
    A portable, submersible, battery-powered water quality probe that performs
    pulsed-LED excited UV-Vis fluorescence and absorbance measurements across
    6 excitation bands (255/280/365/470/590/660 nm) and 4 detection channels to
    quantify CDOM/DOM, chlorophyll-a, phycocyanin (cyanobacteria/HAB), crude-oil
    hydrocarbons, and turbidity in-situ. STM32L4R9 MCU, ADS1256 24-bit ADC,
2026-06-18 Add aerocast: real-time bioaerosol identification & allergy forecast station
2026-06-18 Add pollen-scout: autonomous edge-AI pollen & aerosol forecasting instrument
2026-06-18 Add flora-pulse: Plant Electrophysiology & Sap-Flow Stress Monitor
2026-06-19 Add stratascan: open-source stepped-frequency ground penetrating radar imager
2026-06-22 Add breathprint: portable breath VOC analyzer & metabolic health monitor
2026-06-23 Add mycomesh: 16-channel fungal mycelium electrophysiology & chemical sensing network with edge spike sorting and LoRaWAN mesh telemetry
2026-06-24 Add wattlens: 3-phase power quality analyzer with on-device NILM neural disaggregation
2026-06-25 Add soundloom: bioacoustic soil health monitor with 12-channel geophone array, edge AI classifier, and LoRaWAN telemetry
2026-06-26 Add glaciator-motes: solar-powered wireless microseismometer mesh for glacier monitoring
2026-06-27 Add tremorsense: wearable tremor characterization band with edge ML for Parkinson's monitoring
2026-06-28 Add cryo-sentinel: vendor-agnostic cryogenic Dewar sentinel with cellular alarming
2026-06-29 Add hivevox: acoustic beehive health monitor with LoRaWAN
2026-06-30 Add spectrapest: solar-powered multispectral+acoustic field pest identifier with LoRa mesh networking
